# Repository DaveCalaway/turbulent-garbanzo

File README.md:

# turbulent-garbanzo

**Gemma_discrete_components**

*status*: Beta

DaveCalaway

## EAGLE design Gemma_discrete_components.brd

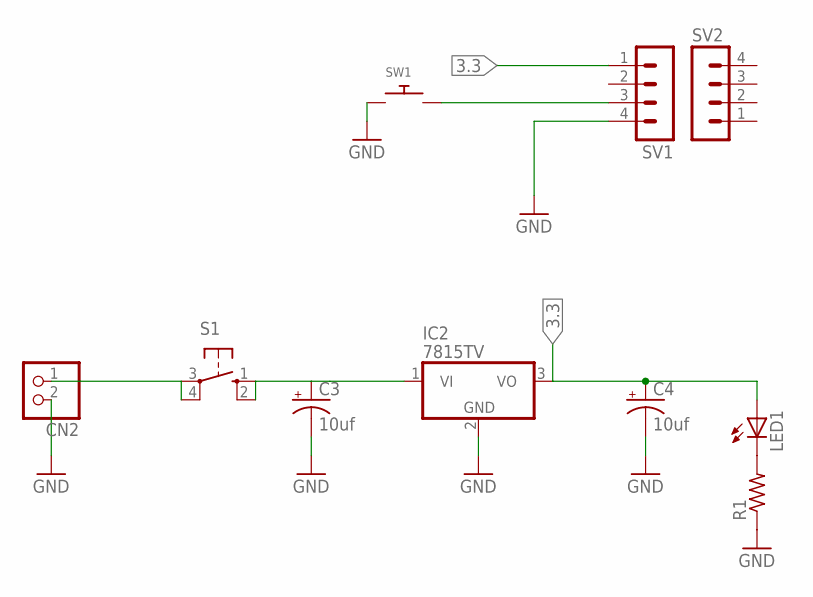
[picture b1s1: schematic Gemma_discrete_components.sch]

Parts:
C3, C4: 10uf; E2,5-6E
CN2: JST_2PIN-THM-RA; JST-PH-2-THM-RA
IC2: 7815TV; TO220V
LED1: LED3MM
R1: R-US_0204/2V; 0204V
S1: 10-XX; B3F-10XX
SV1, SV2: MA04-1
SW1: SWITCH_PUSHBUTTONEVQ-PE; TACT_PANA-EVQ

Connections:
3.3: C4.+, IC2.3 (VO), LED1.A, SV1.1
GND: C3.-, C4.-, CN2.2 (1), IC2.2 (GND), R1.1, SV1.4, SW1.P$1
unnamed: SV1.3, SW1.P$2
unnamed: C3.+, S1.1 (S), S1.2 (S1)
unnamed: LED1.K (C), R1.2
unnamed: CN2.1 (2), S1.3, S1.4 (P1)

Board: 2 copper layers, 10 parts (1 on the bottom side), 6 nets, no tracks yet.

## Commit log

2015-11-16 start
